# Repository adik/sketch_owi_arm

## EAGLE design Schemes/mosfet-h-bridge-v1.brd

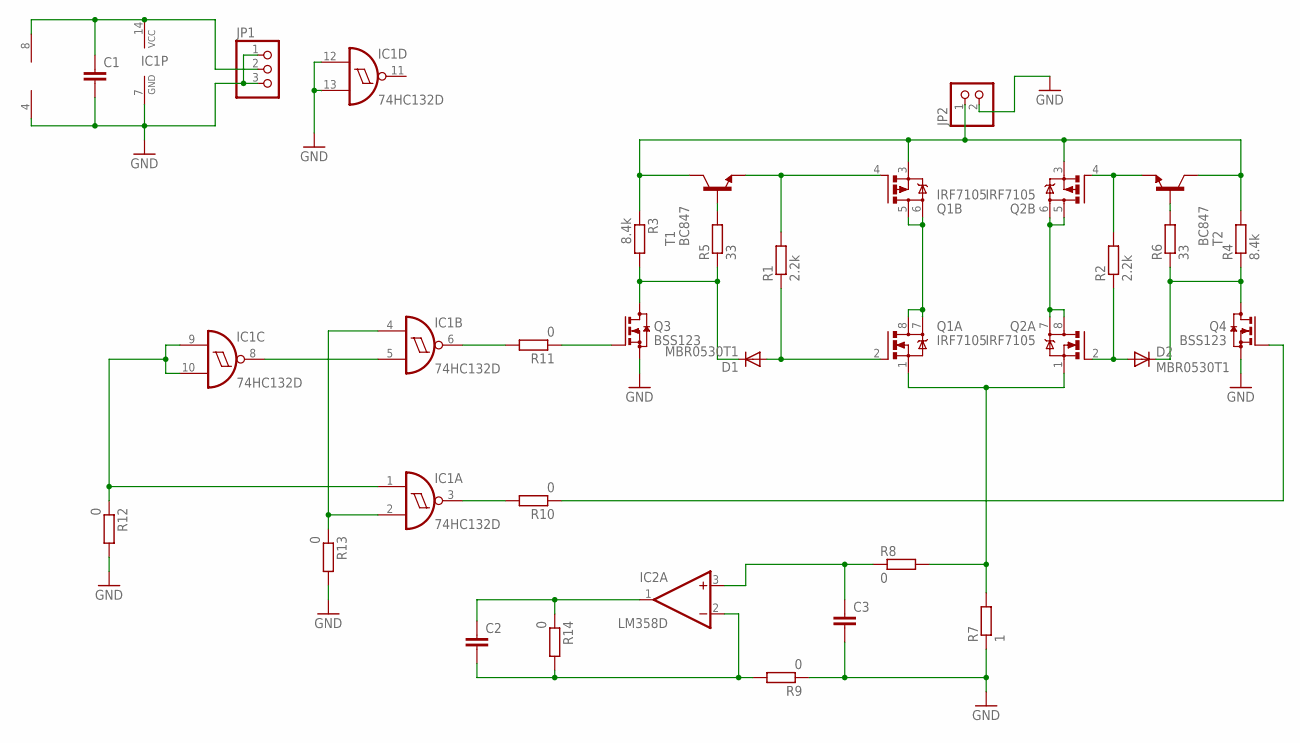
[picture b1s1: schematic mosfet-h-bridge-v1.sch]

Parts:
C1: C-EUC1206K; C1206K
C2, C3: C-EUC1206; C1206
D1, D2: MBR0530T1; SOD123
IC1: 74HC132D; SO14
IC2: LM358D; SO08
JP1: PINHD-1X3; 1X03
JP2: PINHD-1X2; 1X02
Q1, Q2: IRF7105; SO08
Q3, Q4: BSS123; SOT23
R1, R2: 2.2k; R1206S
R3, R4: 8.4k; R1206S
R5, R6: 33; R1206S
R7: 1; R2512
R8, R9, R10, R11, R12, R13, R14: 0; R1206S
T1, T2: BC847; SOT23

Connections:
GND: C1.2, C3.2, IC1.7 (GND), IC1.12 (I0), IC1.13 (I1), IC2.4 (V-), JP1.1, JP1.3, JP2.2, Q3.2 (S), Q4.2 (S), R7.1, R9.1, R12.2, R13.2
unnamed: D1.A, Q1.2 (G), R1.1
unnamed: Q1.5 (D), Q1.6 (D1), Q1.7 (D1), Q1.8 (D)
unnamed: Q1.4 (G), R1.2, T1.2 (E)
unnamed: Q2.4 (G), R2.2, T2.2 (E)
unnamed: Q1.1 (S), Q2.1 (S), R7.2, R8.2
unnamed: D2.A, Q2.2 (G), R2.1
unnamed: D1.C, Q3.3 (D), R3.2, R5.1
unnamed: R5.2, T1.1 (B)
unnamed: JP2.1, Q1.3 (S), Q2.3 (S), R3.1, R4.2, T1.3 (C), T2.3 (C)
unnamed: D2.C, Q4.3 (D), R4.1, R6.1
unnamed: R6.2, T2.1 (B)
unnamed: C3.1, IC2.3 (+IN), R8.1
unnamed: Q2.5 (D), Q2.6 (D1), Q2.7 (D1), Q2.8 (D)
unnamed: C2.2, IC2.2 (-IN), R9.2, R14.2
unnamed: C1.1, IC1.14 (VCC), IC2.8 (V+), JP1.2
unnamed: IC1.6 (O), R11.2
unnamed: Q4.1 (G), R10.1
unnamed: IC1.1 (I0), IC1.9 (I0), IC1.10 (I1), R12.1
unnamed: IC1.2 (I1), IC1.4 (I0), R13.1
unnamed: IC1.5 (I1), IC1.8 (O)
unnamed: IC1.3 (O), R10.2
unnamed: Q3.1 (G), R11.1
unnamed: C2.1, IC2.1 (OUT), R14.1

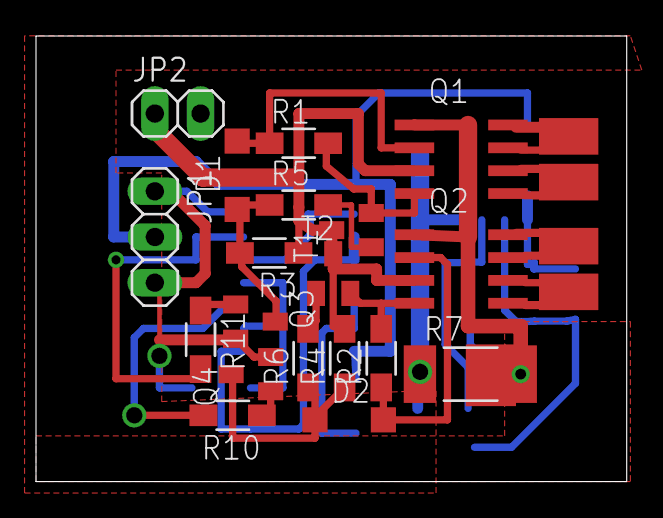
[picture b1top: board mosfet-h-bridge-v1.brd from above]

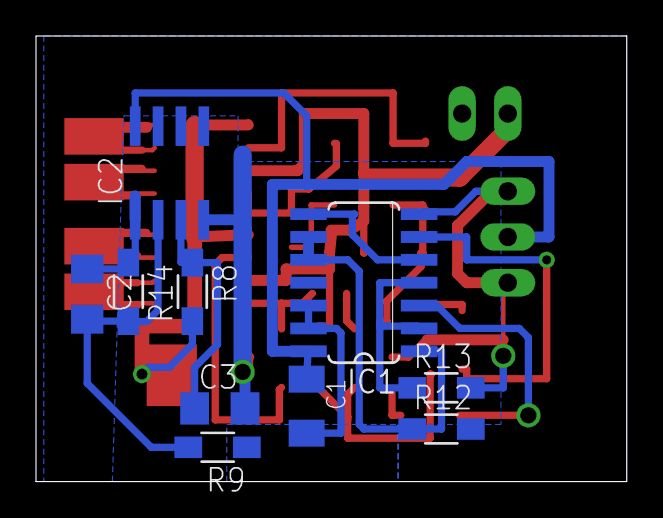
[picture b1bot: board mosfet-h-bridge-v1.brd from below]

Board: 2 copper layers, 32.8 x 24.8 mm, 29 parts (10 on the bottom side), 24 nets.

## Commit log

2012-04-17 New version
2012-07-11 Next version
2012-10-16 added schemes
